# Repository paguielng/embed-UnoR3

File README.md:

<table>
<tr>
<td></td>
</tr>
</table>

    ** Simulation de feu tricolore avec un passage pieton **
    
    feu vert tricolore (voiture) sur broche 10,  allumée pendant 3s
    feu orange tricolore sur broche 11, allumée pendant 1s
    feu rouge tricolore sur broche 12, allumée pendant 3s

    feu Vert bicolore (pieton) sur broche 8
    feu rouge bicolore sur broche 9

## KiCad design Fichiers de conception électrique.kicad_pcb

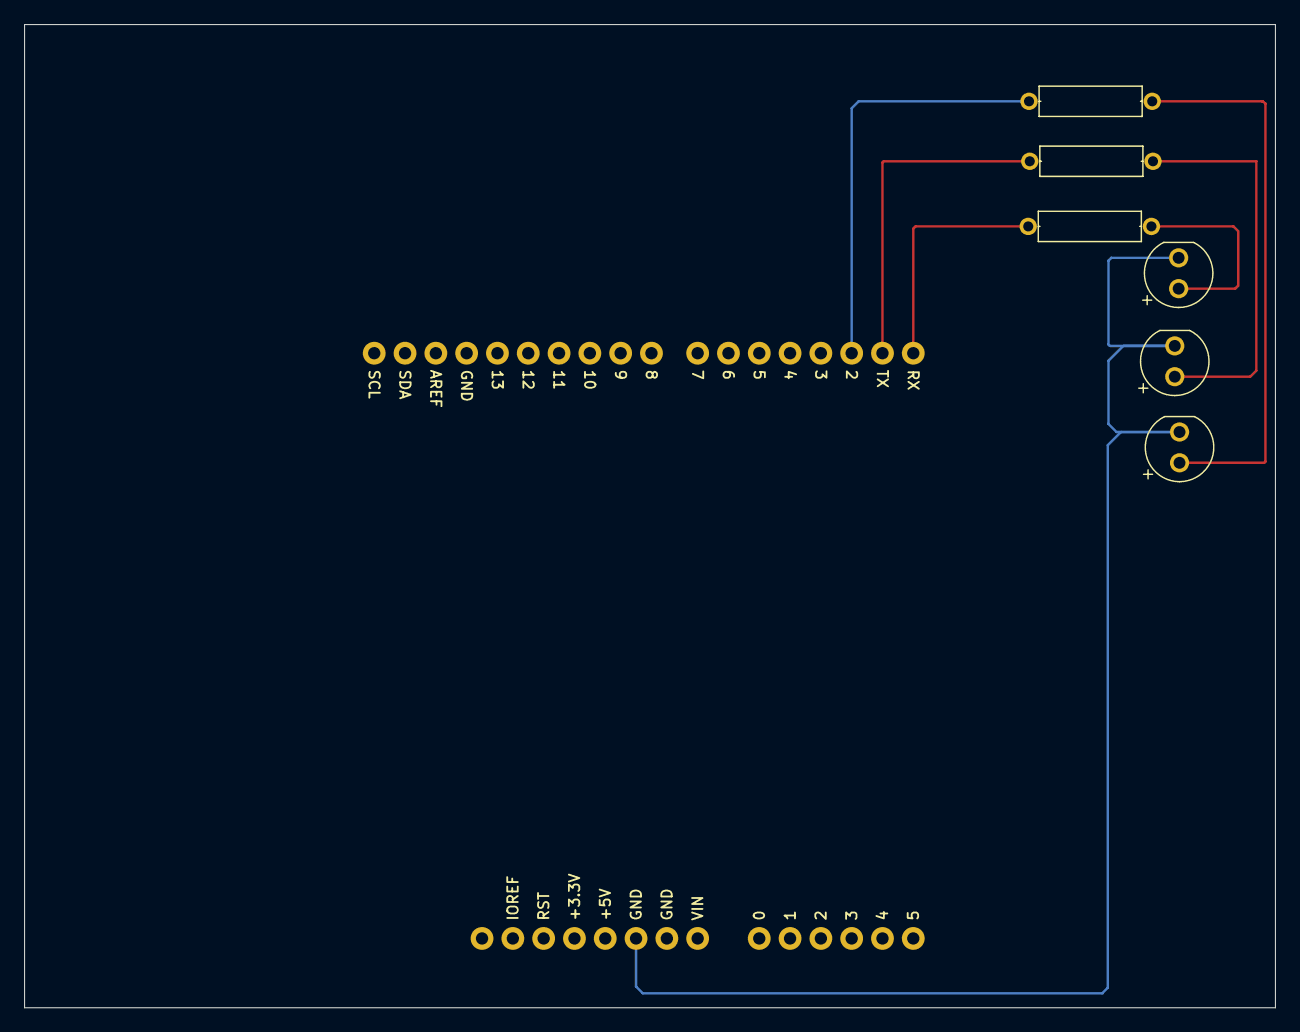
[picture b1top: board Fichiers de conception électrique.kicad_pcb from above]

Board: 2 copper layers, 103.1 x 81.1 mm, 7 parts (0 on the bottom side), 7 nets.

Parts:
D1: LED_RED; LEDRD254W60D565H860B_30890021
D2: LED_ORANGE; LEDRD254W60D565H860B_O_30890021
D3: LED_GREEN; LEDRD254W60D565H860B_G_30890021
R1, R2, R3: 200; RESAD1016W63L850D250B_30890021
U1: ARDUINO-UNO-R3-SHIELD; ARDUINO-UNO-R3-SHIELD_30890021

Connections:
D1_A: D1.1, R1.2
D2_A: D2.1, R2.2
D3_A: D3.1, R3.2
U1_D2: R3.1, U1.D2
U1_GND: D1.2, D2.2, D3.2, U1.GND@0, U1.GND@1, U1.GND@2
U1_RX: R1.1, U1.RX
U1_TX: R2.1, U1.TX

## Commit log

2026-04-20 Rename schématique.pdf to schématique_piétons.pdf
2026-04-20 Rename schématique_piétons.pdf to schématique_pi.pdf
    schématique avec piétons
2026-04-20 Rename schématique_feu.pdf to schématique.pdf
    schématique sans piétons. Mode de base
2026-04-20 Enhance README with table and ASCII art
    Added a table with an image and ASCII art header to the README.
2026-04-20 Update image in README with new cover photo
2026-04-20 Update image width in README table
